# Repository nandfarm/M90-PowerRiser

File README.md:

# M90-PowerRiser
PowerRiser – NVMe 2230 and 2242 Expansion board for Lenovo Tiny 6 Series M90q Gen 1 and 2 and P340 and P350

# Buy preassembled boards:

Best for European locations (EUR currency): </br>

Best for International locations (USD currency): </br>

This is the first ~UNTESTED~ TESTED version of the M90 PowerRiser. Like the previous one it is a custom-designed passive riser board that allows you to break out the proprietary Lenovo Tiny 6 series PCIe connector into a standard open-ended x8 PCIe slot, while also providing an additional M.2 NVMe slot for further storage expansion. This board was specifically designed for select Lenovo Tiny 6 series systems (10th/11th gen), such as:

- ThinkCentre M90q Gen 1 and Gen 2

- ThinkStation P340 Tiny

- ThinkStation P350 Tiny

These boards are compatible with the following Lenovo riser FRU code: 5C50W00877. Basically, this riser will do the same job and will allow you access to an extra 4-lane NVMe M.2 slot, supporting all NVMe M.2 form factors, at PCIe 3.0 speeds.

⚠ Please note: The additional M.2 slot supports only PCIe NVMe drives, not SATA drives.

## Prototype Updates (01/12/2025)

Ok some updates are required. 

The first prototype boards have arrived and I could not wait to solder one to test it. 

~Issue no 1: It appears that the chassy has different folds than the m720q family of devices and the pertruding pins of the FAN connector on the bottom side of the board touch the chassy. This is a problem since no one wants a short so the fan header needs to move somewhere else or, find a surface mount version.~

Issue no 1: Has been solved by moving the connector and rotating it 180 degrees. 

~Issue no 2: I have routed some of the low speed # detect wires poorly and the board was not initially detected by the device. After some adjustments with a box cutter and the soldering iron, the M90q detects both the PCIe PERC and the NVMe SSD. This needs to be corrected in the next hardware version.~

Issue no 2: Has been solved in the latest revision.

~Potential issue no 3: The M90q detects (lspci on Ubuntu) the NVMe but downgrades it to PCIe gen 3 (not 4) (LnkCap says PCIe4 capable and LnkSta says PCIe3 (Downgrade)). R/W speeds are matching PCIe gen 3 speeds and are stable. Not sure if the Tiny is not capable of PCIe gen 4 or there is somethign wrong with my board. The high speed trace impedances have been tested on a signal analyzer and are within spec. Did not find a way to force PCIe gen 4 speeds on the device yet. Will keep investigating.~

Potential issue no 3: Apparently this is normal behaviour as the PCH of this generation of boards is only PCIe 3.0 compatible. So the NVMe SSDs connected to this slot will run at 3.0 speeds and not at 4.0 like the ones on the motherboard. 

---------------------------------------
Other things: 

- There is no way to put the NVMe connector on the side of the riser like the m720q version of the riser since there is no space to place even the 2230 sized NVMe. The good news by putting this vertically on the riser, you can now insert 2280 sized SSDs without space constraints. The bad news is that the vertical M.2 slot can not be sourced easily/cheaply so would add an extra assembly step.
- The position of the M.2 slot is perfectly placed to clear the wifi/BT card and to have the posibility to add a longer card on the x8 PCIe slot AS LONG AS there is nothing under the PCIe board and there is no heatsink on the NVMe. (excuse the bothced fan added to the PERC card :D )

- There seems to be a way to bifurcate the x8 connection in two x4 onnectors without any hardware modiffication on the motherboard. Have to explore this further since this could lead to the ability to connect up to 5 NVMes in one tiny device. Would be great for a NAS with RAID 5.
- 
  ↑ There is and the new board is under test. Will release once it has been thoroughly tested.
- Have to see if the USB2 port is host or device as it could be interesting for those who want to add something extra like a fan speed controller.
- 
  ↑ Will not be implemented in the current version.

I think there is value in creating this riser as it has some cool advantages: 
- you have the space for a 2280 sized SSD
- selectable fan voltage can work at 12v or 5v
- there is the posibility of bifurcation of the x8 pcie without hardware modiffications (imagine 5 NVMes on this machine -> RAID 5 NAS *drooling*)
- extra USB2 connection (not sure if device or host yet) 
- SPI connection to the PCH (have to explore this more in depth)
- no need for clock buffer/divider as the device now breaks out 4x 100MHz clock sources
- there are connections for the power and reset button that could be used if a custom chassy is made.

## Usage & Limitations
You can safely install longer PCIe cards (x16), but electrically the slot remains x8.
The NVMe is no longer installed alongside the Riser board like in the Mx20 version because the proprietary Lenovo connector on the Motherboard is longer and the height does not allow it. This means that there may be interference between the NVMe and other adapters that can be inserted in the WIFI/BT port. (testing needs to be done.

NVMe drives supported: 2230, 2242 and 2260 (2280 not tested during mockup).

This riser is only compatible with the Lenovo Tiny 6 series models listed above.

SATA M.2 drives are not supported on the added M.2 slot.

The riser is capable of accepting x16 PCIe boards but in order for them to be detected, the "PCIe_Detect" solder bridge on the back needs to be bridged.

## Project Origin & Intent
This project was built from personal need, trial, and experimentation. 

## License
This project is licensed under the CERN Open Hardware License v2 - Strongly Reciprocal (CERN-OHL-S).

You are free to:

- Manufacture and assemble this board.

- Use it in your own projects.

- Modify and improve it.

However, any modifications and derived works must also be distributed under the same license and atributed.

For full license terms, please refer to [CERN-OHL-S](https://ohwr.org/project/cernohl/wikis/home).

## Disclaimer
⚠ Use at your own risk.
By using, manufacturing, or assembling this board, you accept that:

I am not responsible for any damages, whether physical, financial, or mental, arising from its use.

The design has been made available for educational, experimental, and hobbyist purposes.

Always double-check compatibility, power requirements, and mechanical fit before installation.

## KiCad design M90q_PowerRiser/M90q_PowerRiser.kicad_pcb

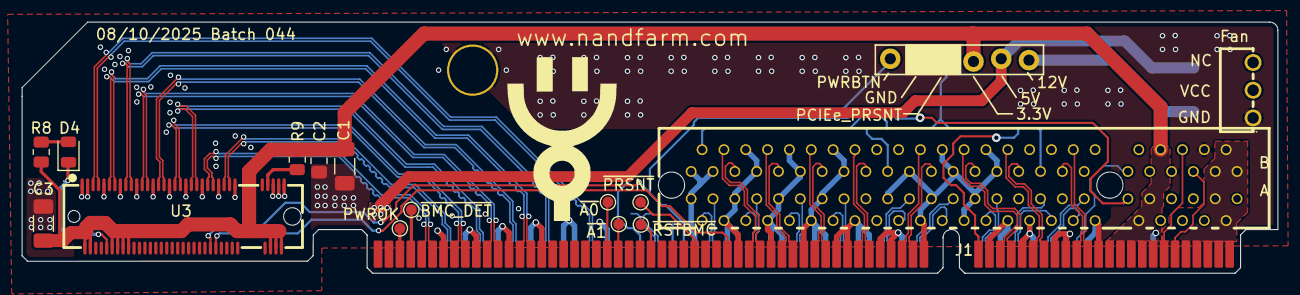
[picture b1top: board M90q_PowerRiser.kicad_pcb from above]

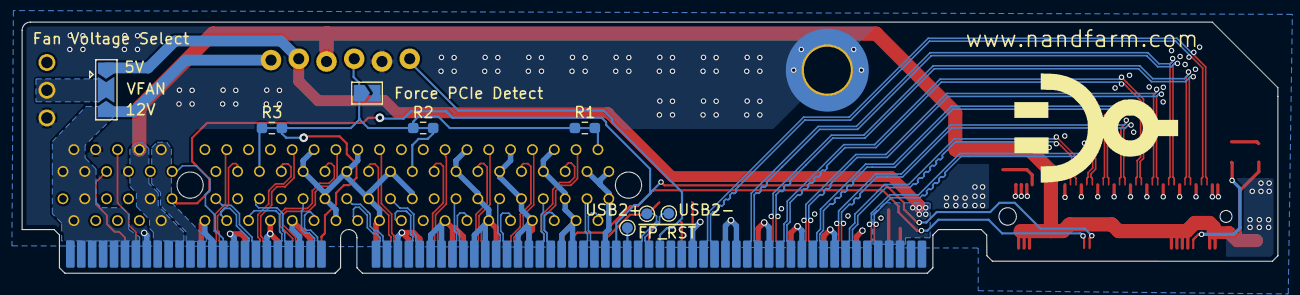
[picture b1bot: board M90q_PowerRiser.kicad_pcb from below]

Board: 4 copper layers, 115.0 x 23.0 mm, 26 parts (9 on the bottom side), 77 nets.

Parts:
3P_FAN1: 2510-3AW_C22451143; CONN-TH_2510-3AW
AUX1: Conn_01x06; 1x06_P2.54mm_Locking
C1, C3: 47u; C_1206_3216Metric_Pad1.33x1.80mm_HandSolder
C2: 100n; C_0805_2012Metric_Pad1.18x1.45mm_HandSolder
D4: LED; LED_0805_2012Metric
H_Mount1: MountingHole_Pad; MountingHole_4.3mm_M4_ISO7380_Pad_TopOnly
J1: Bus_PCI_Express_x8; CONN-TH_98P-P1.00-V_3183-XXXXXPXT
JP1: SolderJumper_3_Open; SolderJumper-3_P2.0mm_Open_TrianglePad1.0x1.5mm
JP2: Force_PCIe_Detect; SolderJumper-2_P1.3mm_Open_TrianglePad1.0x1.5mm
R1, R2, R3: 0R; R_0603_1608Metric_Pad0.98x0.95mm_HandSolder
R8: 220; R_0805_2012Metric
R9: 10k; R_0805_2012Metric
TP1: USB2-; TestPoint_Pad_D1.0mm
TP2: USB2+; TestPoint_Pad_D1.0mm
TP3: PWROK; TestPoint_Pad_D1.0mm
TP4: ~{A0}; TestPoint_Pad_D1.0mm
TP5: ~{A1}; TestPoint_Pad_D1.0mm
TP6: ~{RSTBMC}; TestPoint_Pad_D1.0mm
TP7: ~{PRSNT}; TestPoint_Pad_D1.0mm
TP8: ~{FP_RST}; TestPoint_Pad_D1.0mm
TP9: ~{BMC_DET}; TestPoint_Pad_D1.0mm
U1: M90q_PCIe
U3: HYCW19M-05NGFF-530B; CONN-SMD_HYCW19M-05NGFF-530B

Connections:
+3V3: AUX1.3, C1.1, C2.1, C3.1, J1.A9 (+3.3V), J1.A10 (+3.3V), J1.B8 (+3.3V), R8.2, R9.1, U1.A64 (3V3), U1.A65 (3V3), U1.A66 (3V3), U1.A67 (3V3), U1.A68 (3V3), U1.B65 (3V3), U1.B66 (3V3), U1.B67 (3V3), U3.2, U3.4, U3.12, U3.14, U3.16, U3.18, U3.70, U3.72, U3.74
+3V3_S: J1.B10 (3.3Vaux), U1.B63 (3V3_S), U1.B64 (3V3_S)
+5V_S: AUX1.2, JP1.1 (A), U1.B3 (5V_S), U1.B4 (5V_S), U1.B5 (5V_S)
+12V: AUX1.1, J1.A2 (+12V), J1.A3 (+12V), J1.B1 (+12V), J1.B2 (+12V), J1.B3 (+12V), JP1.3 (B), U1.A71 (12V), U1.A72 (12V), U1.A73 (12V), U1.A74 (12V), U1.A75 (12V), U1.B69 (12V), U1.B70 (12V), U1.B71 (12V), U1.B72 (12V), U1.B73 (12V), U1.B74 (12V), U1.B75 (12V)
CLK_SLOT4X_100M+: U1.B7 (CLK_SLOT4X_100M+), U3.55
CLK_SLOT4X_100M-: U1.B8 (CLK_SLOT4X_100M-), U3.53
CLK_SLOT8X_100M_0+: J1.A13 (REFCLK+), U1.B58 (CLK_SLOT8X_100M_0+)
CLK_SLOT8X_100M_0-: J1.A14 (REFCLK-), U1.B59 (CLK_SLOT8X_100M_0-)
GND: 3P_FAN1.1, AUX1.5, C1.2, C2.2, C3.2, H_Mount1.1, J1.A1 (~PRSNT1), J1.A4 (GND), J1.A12 (GND), J1.A15 (GND), J1.A18 (GND), J1.A20 (GND), J1.A23 (GND), J1.A24 (GND), J1.A27 (GND), J1.A28 (GND), J1.A31 (GND), J1.A34 (GND), J1.A37 (GND), J1.A38 (GND), J1.A41 (GND), J1.A42 (GND), J1.A45 (GND), J1.A46 (GND), J1.A49 (GND), J1.B4 (GND), J1.B7 (GND), J1.B13 (GND), J1.B16 (GND), J1.B18 (GND), J1.B21 (GND), J1.B22 (GND), J1.B25 (GND), J1.B26 (GND), J1.B29 (GND), J1.B32 (GND), J1.B35 (GND), J1.B36 (GND), J1.B39 (GND), J1.B40 (GND), J1.B43 (GND), J1.B44 (GND), J1.B47 (GND), J1.B49 (GND), JP2.2 (B), U1.A7 (GND), U1.A10 (GND), U1.A13 (GND), U1.A16 (GND), U1.A34 (GND), U1.A37 (GND), U1.A40 (GND), U1.A43 (GND), U1.A44 (GND), U1.A47 (GND), U1.A48 (GND), U1.A51 (GND), U1.A53 (GND), U1.A56 (GND), U1.A59 (GND), U1.A60 (GND), U1.A63 (GND), U1.B9 (GND), U1.B12 (GND), U1.B15 (GND), U1.B18 (GND), U1.B19 (GND), U1.B22 (GND), U1.B30 (GND), U1.B33 (GND), U1.B34 (GND), U1.B37 (GND), U1.B38 (GND), U1.B41 (GND), U1.B42 (GND), U1.B45 (GND), U1.B46 (GND), U1.B49 (GND), U1.B54 (GND), U1.B57 (GND), U1.B60 (GND), U1.B62 (GND), U1.B68 (GND), U3.1, U3.3, U3.9, U3.15, U3.21, U3.27, U3.33, U3.39, U3.45, U3.51, U3.57, U3.71, U3.73, U3.75
NVME_PRX_DTX_0+: U1.B11 (NVME_PRX_DTX_0+), U3.43
NVME_PRX_DTX_0-: U1.B10 (NVME_PRX_DTX_0-), U3.41
NVME_PRX_DTX_1+: U1.B13 (NVME_PRX_DTX_1+), U3.31
NVME_PRX_DTX_1-: U1.B14 (NVME_PRX_DTX_1-), U3.29
NVME_PRX_DTX_2+: U1.B17 (NVME_PRX_DTX_2+), U3.19
NVME_PRX_DTX_2-: U1.B16 (NVME_PRX_DTX_2-), U3.17
NVME_PRX_DTX_3+: U1.B20 (NVME_PRX_DTX_3+), U3.7
NVME_PRX_DTX_3-: U1.B21 (NVME_PRX_DTX_3-), U3.5
NVME_PTX_DRX_0+: U1.A5 (NVME_PTX_DRX_0+), U3.49
NVME_PTX_DRX_0-: U1.A6 (NVME_PTX_DRX_0-), U3.47
NVME_PTX_DRX_1+: U1.A9 (NVME_PTX_DRX_1+), U3.37
NVME_PTX_DRX_1-: U1.A8 (NVME_PTX_DRX_1-), U3.35
NVME_PTX_DRX_2+: U1.A12 (NVME_PTX_DRX_2+), U3.25
NVME_PTX_DRX_2-: U1.A11 (NVME_PTX_DRX_2-), U3.23
NVME_PTX_DRX_3+: U1.A15 (NVME_PTX_DRX_3+), U3.13
NVME_PTX_DRX_3-: U1.A14 (NVME_PTX_DRX_3-), U3.11
unnamed: D4.2 (A), R8.1
unnamed: D4.1 (K), U3.10
unnamed: R9.2, U3.69
PCH_SYSPWROK: TP3.1, U1.A3 (PCH_SYSPWROK)
PCIE_CRX_DTX_0+: J1.A16 (PERp0), U1.B56 (PCIE_CRX_DTX_0+)
PCIE_CRX_DTX_0-: J1.A17 (PERn0), U1.B55 (PCIE_CRX_DTX_0-)
PCIE_CRX_DTX_1+: J1.A21 (PERp1), U1.B53 (PCIE_CRX_DTX_1+)
PCIE_CRX_DTX_1-: J1.A22 (PERn1), U1.B52 (PCIE_CRX_DTX_1-)
PCIE_CRX_DTX_2+: J1.A25 (PERp2), U1.B50 (PCIE_CRX_DTX_2+)
PCIE_CRX_DTX_2-: J1.A26 (PERn2), U1.B51 (PCIE_CRX_DTX_2-)
PCIE_CRX_DTX_3+: J1.A29 (PERp3), U1.B47 (PCIE_CRX_DTX_3+)
PCIE_CRX_DTX_3-: J1.A30 (PERn3), U1.B48 (PCIE_CRX_DTX_3-)
PCIE_CRX_DTX_4+: J1.A35 (PERp4), U1.B44 (PCIE_CRX_DTX_4+)
PCIE_CRX_DTX_4-: J1.A36 (PERn4), U1.B43 (PCIE_CRX_DTX_4-)
PCIE_CRX_DTX_5+: J1.A39 (PERp5), U1.B40 (PCIE_CRX_DTX_5+)
PCIE_CRX_DTX_5-: J1.A40 (PERn5), U1.B39 (PCIE_CRX_DTX_5-)
PCIE_CRX_DTX_6+: J1.A43 (PERp6), U1.B36 (PCIE_CRX_DTX_6+)
PCIE_CRX_DTX_6-: J1.A44 (PERn6), U1.B35 (PCIE_CRX_DTX_6-)
PCIE_CRX_DTX_7+: J1.A47 (PERp7), U1.B32 (PCIE_CRX_DTX_7+)
PCIE_CRX_DTX_7-: J1.A48 (PERn7), U1.B31 (PCIE_CRX_DTX_7-)
PCIE_CTX_DRX_0+: J1.B14 (PETp0), U1.A62 (PCIE_CTX_DRX_0+)
PCIE_CTX_DRX_0-: J1.B15 (PETn0), U1.A61 (PCIE_CTX_DRX_0-)
PCIE_CTX_DRX_1+: J1.B19 (PETp1), U1.A58 (PCIE_CTX_DRX_1+)
PCIE_CTX_DRX_1-: J1.B20 (PETn1), U1.A57 (PCIE_CTX_DRX_1-)
PCIE_CTX_DRX_2+: J1.B23 (PETp2), U1.A55 (PCIE_CTX_DRX_2+)
PCIE_CTX_DRX_2-: J1.B24 (PETn2), U1.A54 (PCIE_CTX_DRX_2-)
PCIE_CTX_DRX_3+: J1.B27 (PETp3), U1.A50 (PCIE_CTX_DRX_3+)
PCIE_CTX_DRX_3-: J1.B28 (PETn3), U1.A49 (PCIE_CTX_DRX_3-)
PCIE_CTX_DRX_4+: J1.B33 (PETp4), U1.A46 (PCIE_CTX_DRX_4+)
PCIE_CTX_DRX_4-: J1.B34 (PETn4), U1.A45 (PCIE_CTX_DRX_4-)
PCIE_CTX_DRX_5+: J1.B37 (PETp5), U1.A42 (PCIE_CTX_DRX_5+)
PCIE_CTX_DRX_5-: J1.B38 (PETn5), U1.A41 (PCIE_CTX_DRX_5-)
PCIE_CTX_DRX_6+: J1.B41 (PETp6), U1.A39 (PCIE_CTX_DRX_6+)
PCIE_CTX_DRX_6-: J1.B42 (PETn6), U1.A38 (PCIE_CTX_DRX_6-)
PCIE_CTX_DRX_7+: J1.B45 (PETp7), U1.A36 (PCIE_CTX_DRX_7+)
PCIE_CTX_DRX_7-: J1.B46 (PETn7), U1.A35 (PCIE_CTX_DRX_7-)
SMBCLK_X8: J1.B5 (SMCLK), U1.A70 (SMBCLK_PCIEX8)
SMBDATA_X8: J1.B6 (SMDAT), U1.A69 (SMBDATA_PCIEX8)
USB2+: TP2.1, U1.B27 (USB20+)
USB2-: TP1.1, U1.B26 (USB20-)
VFAN: 3P_FAN1.2, JP1.2 (C)
~BMC_DETECT: TP9.1, U1.A4 (~BMC_DETECT)
~CLK_REQ0_PCIE_X8: AUX1.4, J1.B17 (~PRSNT2), J1.B31 (~PRSNT2), J1.B48 (~PRSNT2), JP2.1 (A), R1.1, R1.2, R2.1, R2.2, R3.1, R3.2, U1.A52 (~CLK_REQ0_PCIE_X8)
~CLK_REQ2_SLOT_X4: U1.A33 (~CLK_REQ2_SLOT_X4), U3.50
~ESPI_ALERT0: TP4.1, U1.A22 (~ESPI_ALERT0)
~ESPI_ALERT1: TP5.1, U1.A23 (~ESPI_ALERT1)
~ESPI_RESET_BMC: TP6.1, U1.A26 (~ESPI_RESET_BMC)
~FP_RST: TP8.1, U1.B28 (~FP_RST)
~PCIERST: J1.A11 (~PERST), U1.B29 (~PCIERST), U3.48
~PCIEX8_WAKE: J1.B11 (~WAKE), U1.B61 (~PCIEX8_WAKE)
~PCIE_X8_X4_PRSNT: TP7.1, U1.A30 (~PCIE_X8_X4_PRSNT)
~PWRBTN: AUX1.6, U1.B25 (~PWRBTN)

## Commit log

2025-10-08 Initial upload
2025-10-08 Photos
2025-10-08 License
2025-10-27 more photos of the first version of the prototype
2025-10-27 Document prototype updates and testing issues
    Added prototype updates and issues encountered during testing.
2025-10-27 Update README with board images and NVMe info
    Added images of the board and clarified NVMe installation details.
2025-12-06 Revise prototype updates and issue resolutions
    Updated prototype issues and resolutions in README.
2025-12-06 Change version status from UNTESTED to TESTED
    Updated the README to reflect the version status of the M90 PowerRiser.
2025-12-06 Revise issue summaries and solutions in README
    Updated issue descriptions and resolutions in README.
2025-12-06 Update README with Tindie badge and testing status
    Added a Tindie store badge and updated the project description to reflect testing status.
2026-04-18 Update README with store links
    Added links to Lectronz and Tindie stores in README.
2026-05-23 Update README with purchasing options for boards
    Added links for purchasing preassembled boards for European and International customers.
2026-05-23 Tidy up file names and readmes
2026-05-23 Update README with riser compatibility details
    Added compatibility information for Lenovo riser FRU code.
